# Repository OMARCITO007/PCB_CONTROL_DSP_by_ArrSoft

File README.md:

# PCB_CONTRO_DSP_by_ArrSoft
PCB 
Eagle 2019
Old_versión, eagle 7.xx

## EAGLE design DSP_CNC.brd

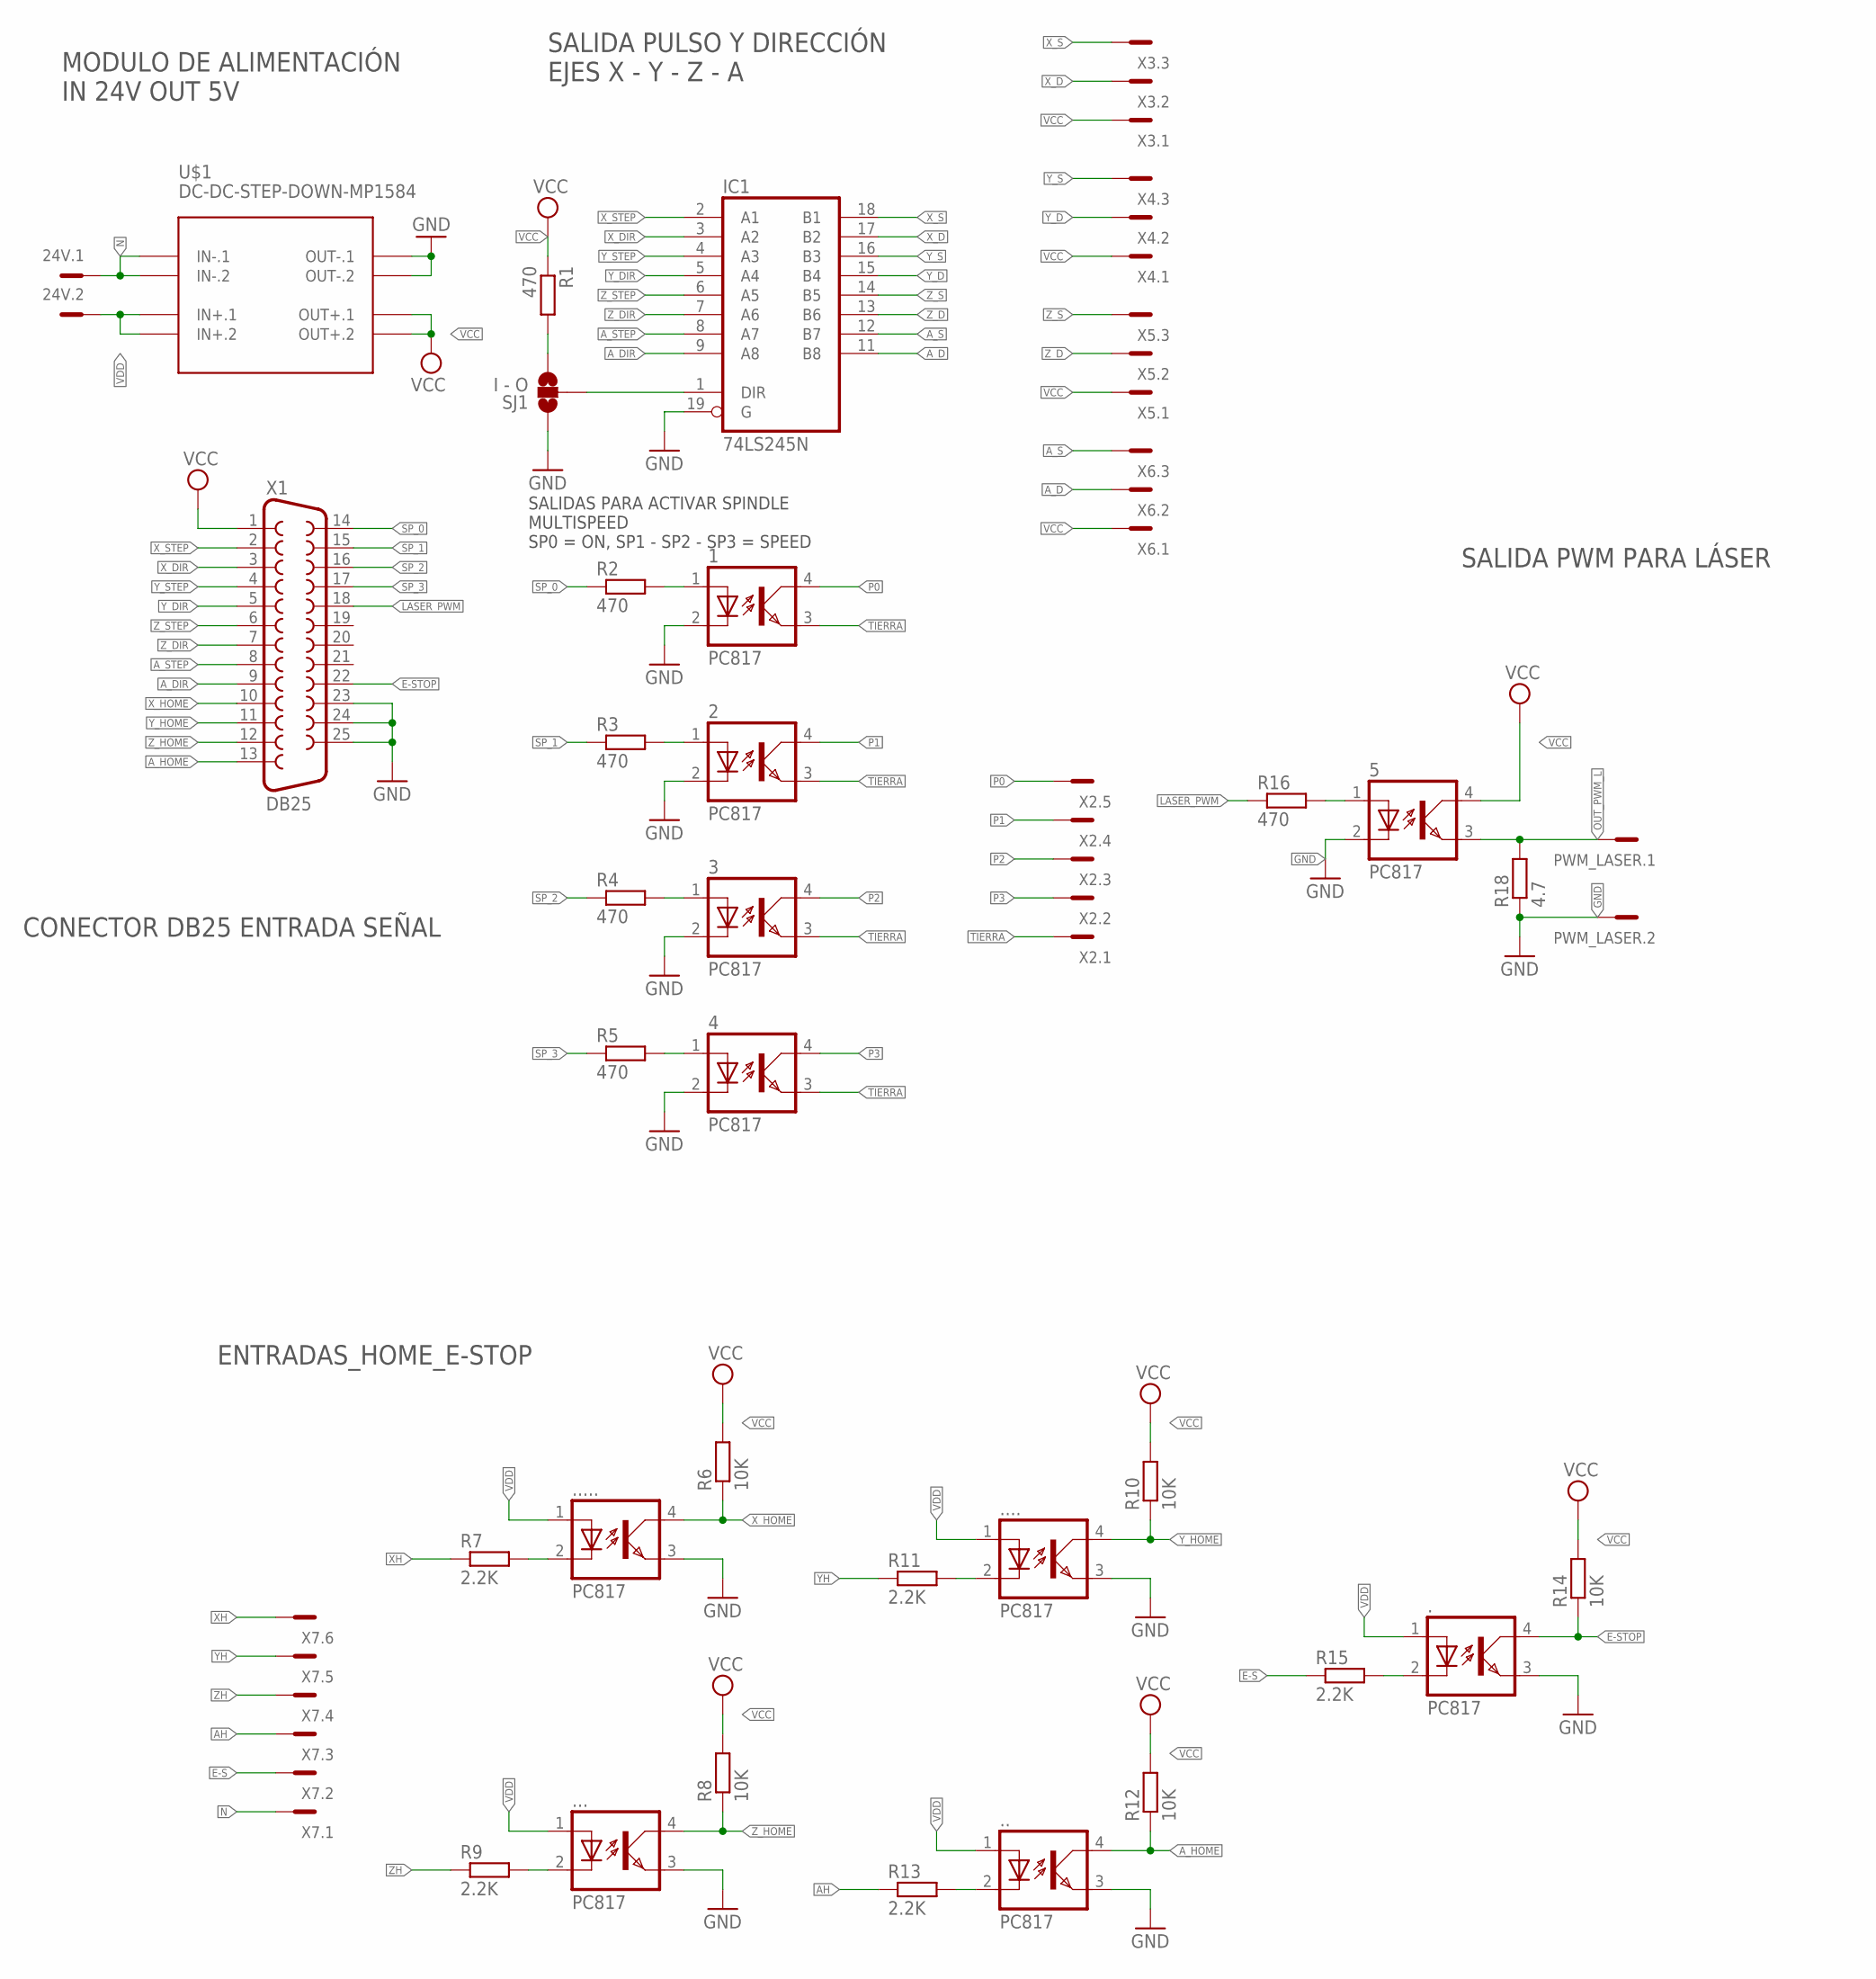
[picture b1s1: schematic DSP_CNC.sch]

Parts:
1, 2, 3, 4, 5, ., .., ..., ...., .....: PC817; DIL04
24V: MCV2
IC1: 74LS245N; DIL20
PWM_LASER: MCV2
R1, R2, R3, R4, R5, R16: 470; 0207/10
R6, R8, R10, R12, R14: 10K; 0207/10
R7, R9, R11, R13, R15: 2.2K; 0207/10
R18: 4.7; 0207/10
SJ1: I - O; SJ_2W
U$1: DC-DC-STEP-DOWN-MP1584
X1: DB25; F25HP
X2: SPINDLE ON - SP123; MCV5
X3: EJE_X; MCV3
X4: EJE_Y; MCV3
X5: EJE_Z; MCV3
X6: EJE_A; MCV3
X7: INPUT_HOME_E-STOP; MCV6

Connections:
AH: R13.1, X7.3
A_D: IC1.11 (B8), X6.2
A_DIR: IC1.9 (A8), X1.9
A_HOME: ...4 (COL), R12.1, X1.13
A_S: IC1.12 (B7), X6.3
A_STEP: IC1.8 (A7), X1.8
E-S: R15.1, X7.2
E-STOP: ..4 (COL), R14.1, X1.22
GND: 1.2 (C), 2.2 (C), 3.2 (C), 4.2 (C), 5.2 (C), ..3 (EMIT), ...3 (EMIT), ....3 (EMIT), .....3 (EMIT), ......3 (EMIT), IC1.10 (GND), IC1.19 (G), PWM_LASER.2, R18.1, SJ1.1, U$1.OUT-.1, U$1.OUT-.2, X1.23, X1.24, X1.25
LASER_PWM: R16.1, X1.18
N: 24V.1, U$1.IN-.1, U$1.IN-.2, X7.1
unnamed: 5.1 (A), R16.2
unnamed: R1.2, SJ1.3
unnamed: IC1.1 (DIR), SJ1.2
unnamed: 2.1 (A), R3.2
unnamed: 1.1 (A), R2.2
unnamed: 3.1 (A), R4.2
unnamed: 4.1 (A), R5.2
unnamed: ......2 (C), R7.2
unnamed: ....2 (C), R9.2
unnamed: .....2 (C), R11.2
unnamed: ...2 (C), R13.2
unnamed: ..2 (C), R15.2
OUT_PWM_L: 5.3 (EMIT), PWM_LASER.1, R18.2
P0: 1.4 (COL), X2.5
P1: 2.4 (COL), X2.4
P2: 3.4 (COL), X2.3
P3: 4.4 (COL), X2.2
SP_0: R2.1, X1.14
SP_1: R3.1, X1.15
SP_2: R4.1, X1.16
SP_3: R5.1, X1.17
TIERRA: 1.3 (EMIT), 2.3 (EMIT), 3.3 (EMIT), 4.3 (EMIT), X2.1
VCC: 5.4 (COL), IC1.20 (VCC), R1.1, R6.2, R8.2, R10.2, R12.2, R14.2, U$1.OUT+.1, U$1.OUT+.2, X1.1, X3.1, X4.1, X5.1, X6.1
VDD: 24V.2, ..1 (A), ...1 (A), ....1 (A), .....1 (A), ......1 (A), U$1.IN+.1, U$1.IN+.2
XH: R7.1, X7.6
X_D: IC1.17 (B2), X3.2
X_DIR: IC1.3 (A2), X1.3
X_HOME: ......4 (COL), R6.1, X1.10
X_S: IC1.18 (B1), X3.3
X_STEP: IC1.2 (A1), X1.2
YH: R11.1, X7.5
Y_D: IC1.15 (B4), X4.2
Y_DIR: IC1.5 (A4), X1.5
Y_HOME: .....4 (COL), R10.1, X1.11
Y_S: IC1.16 (B3), X4.3
Y_STEP: IC1.4 (A3), X1.4
ZH: R9.1, X7.4
Z_D: IC1.13 (B6), X5.2
Z_DIR: IC1.7 (A6), X1.7
Z_HOME: ....4 (COL), R8.1, X1.12
Z_S: IC1.14 (B5), X5.3
Z_STEP: IC1.6 (A5), X1.6

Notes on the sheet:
CONECTOR DB25 ENTRADA SEÑAL
ENTRADAS_HOME_E-STOP
SALIDAS PARA ACTIVAR SPINDLE MULTISPEED SP0 = ON, SP1 - SP2 - SP3 = SPEED
SALIDA PWM PARA LÁSER
SALIDA PULSO Y DIRECCIÓN EJES X - Y - Z - A
MODULO DE ALIMENTACIÓN IN 24V OUT 5V

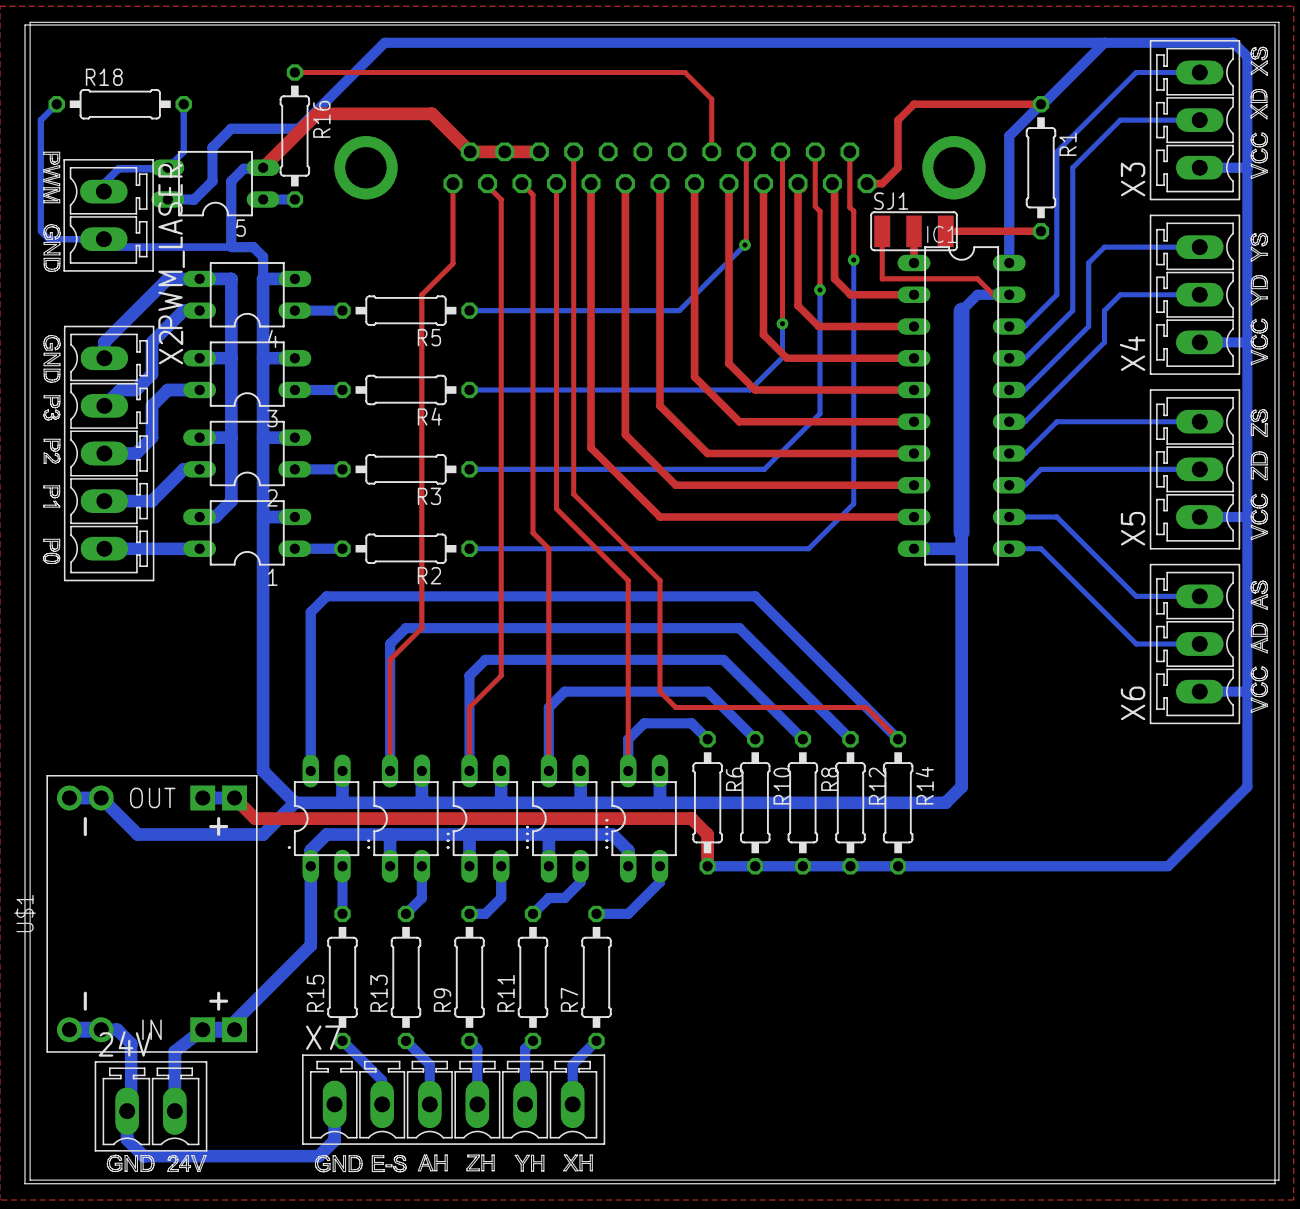
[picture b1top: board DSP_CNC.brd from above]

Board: 2 copper layers, 100.0 x 92.7 mm, 39 parts (1 on the bottom side), 53 nets.

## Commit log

2019-02-21 Create Old_Version
2019-02-21 Set theme jekyll-theme-leap-day

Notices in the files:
parts and their libraries:
SparkFun: Licensing: CC v3.0 Share-Alike You are welcome to use this library for commercial purposes.
diy-modules: Released under the Creative Commons Attribution 4.0 International License: http://creativecommons.org/licenses/by/4.0
